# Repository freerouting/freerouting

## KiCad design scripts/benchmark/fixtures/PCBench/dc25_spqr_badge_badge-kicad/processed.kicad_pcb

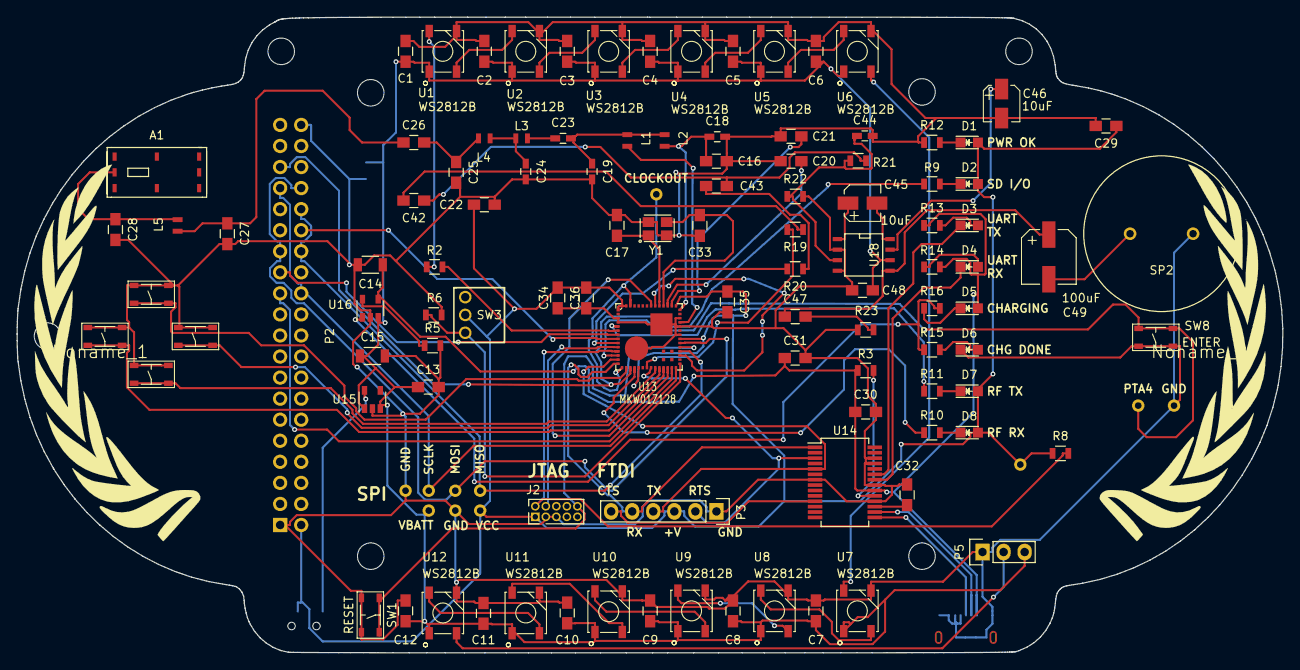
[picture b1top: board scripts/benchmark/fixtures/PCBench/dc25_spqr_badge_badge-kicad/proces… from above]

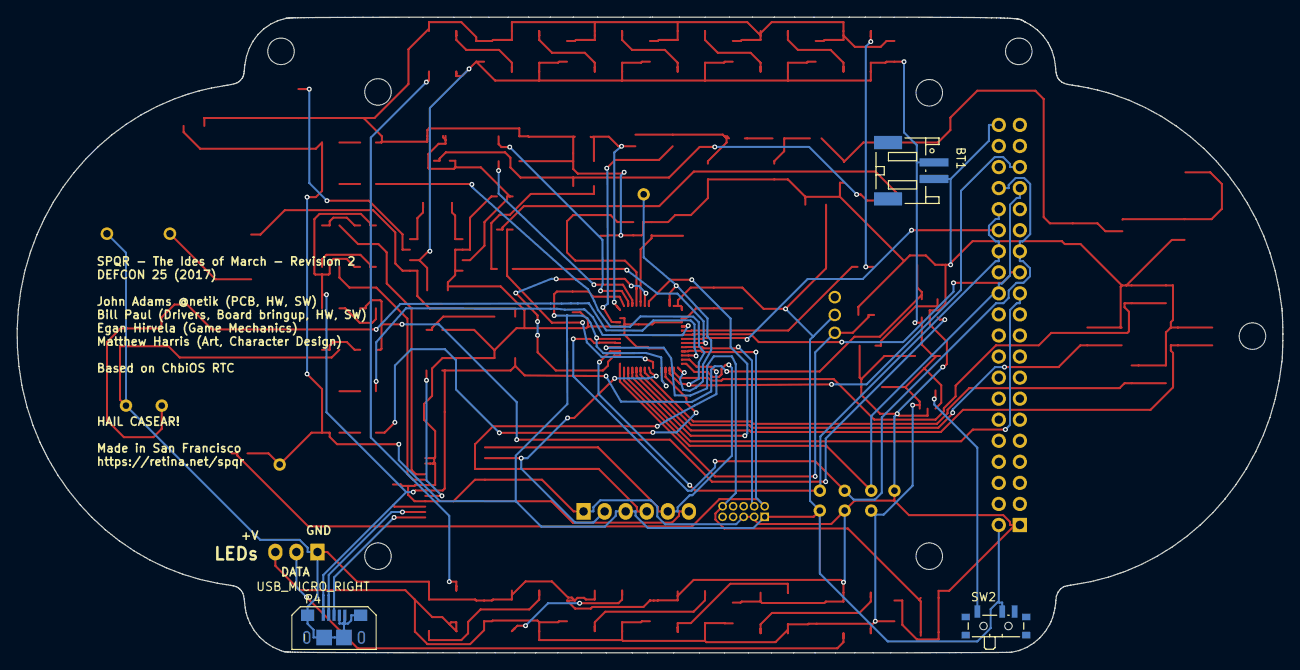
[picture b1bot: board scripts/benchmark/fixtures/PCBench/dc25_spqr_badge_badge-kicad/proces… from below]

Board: 2 copper layers, 152.7 x 76.7 mm, 129 parts (3 on the bottom side), 84 nets.

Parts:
A1: 7488910092_ANTENNA; Antenna_Wurth_7488910092
BT1: Battery 3.7v 1000mAh; JST_PH_S2B-PH-SM4-TB_02x2.00mm_Angled
C1, C2, C3, C4, C5, C6, C7, C8, C9, C10, C11, C12, C20, C21, C22, C30, C32, C34, C35, C36: 0.1uF; C_0805_HandSoldering
C13, C29: 1uF; C_0805_HandSoldering
C14, C15: 10uF; C_1206
C16: 220pF; C_0805_HandSoldering
C17, C33: 11pF; C_0805_HandSoldering
C18, C44: 0.01uF; C_0603_HandSoldering
C19: 2pF; C_0603_HandSoldering
C23: 6.8pF; C_0603_HandSoldering
C24: 7.5pF; C_0603_HandSoldering
C25: 5.6pF; C_0805_HandSoldering
C26: 100pF; C_0805_HandSoldering
C27: 1.2pF; C_0805_HandSoldering
C28: 3.3pF; C_0805_HandSoldering
C31, C42, C43, C48: 10uF; C_0805_HandSoldering
C45, C46: 10uF; MF_Passives-CP4MM
C47: .047uF; C_0805_HandSoldering
C49: 100uF; MF_Passives-CP6.3MM
D1: RED PWROK; LED_0805
D2: GREEN SDIO; LED_0805
D3: RED UTX; LED_0805
D4: GREEN URX; LED_0805
D5: RED (CHARGING); LED_0805
D6: GRN (DONE); LED_0805
D7: RED RFTX; LED_0805
D8: GRN RFRX; LED_0805
H1, H2, H3, H4, H5, H6, H7: CONN_01X01; MountingHole_3.2mm_M3_DIN965
J2: JTAG; Pin_Header_Straight_2x05_Pitch1.27mm
L1: 4.7nH; Neosid_Inductor_SM0603CG
L2: 33nH; Neosid_Inductor_SM0603CG
L3, L4: 0.0068 uH; Neosid_Inductor_SM0603CG
L5: 15nH; Neosid_Inductor_SM0603CG
Noname_1: laurel
Noname_2: laurel_right
P2: CONN_02X20; IDC_HEADER_FEMALE
P3: FTDI BACKUP; Pin_Header_Straight_1x06
P4: USB_MICRO_RIGHT; MF_Connectors-MICROUSB-RIGHT
P5: LED OUT (DNP); Pin_Header_Straight_1x03
R2: 100; R_0805
R3, R6, R23: 10k; R_0805
R5: 2k; R_0805
R8: 10K; R_0805
R9, R10, R11, R12: 220; R_0805
R13, R14, R15, R16, R19, R20, R22: 1k; R_0805
R21: 100k; R_0805
SP2: MODEL TBD; SPEAKER_AST_01708MR_R
SW1: RESET; MF_Switches-TACT4.2MM
SW2: POWERON; SW_SPDT_PCM12
SW3: TM1000
SW4: UP; MF_Switches-TACT4.2MM
SW5: DN; MF_Switches-TACT4.2MM
SW6: LEFT; MF_Switches-TACT4.2MM
SW7: RIGHT; MF_Switches-TACT4.2MM
SW8: ENTER; MF_Switches-TACT4.2MM
TP1: PTA4; Measurement_Point_Round-TH_Small
TP2, TP5, TP10: GND; Measurement_Point_Round-TH_Small
TP3, TP9: VCC; Measurement_Point_Round-TH_Small
TP4: VBAT; Measurement_Point_Round-TH_Small
TP17: SPI_CH1_SCLK; Measurement_Point_Round-TH_Small
TP18: CLOCKOUT; Measurement_Point_Round-TH_Small
TP19: SPI_CH1_MOSI; Measurement_Point_Round-TH_Small
TP20: SPI_CH1_MISO; Measurement_Point_Round-TH_Small
U1, U2, U3, U4, U5, U6, U7, U8, U9, U10, U11, U12: WS2812B; MF_LEDs-WS2812B
U13: MKW01Z128; 98ASA00302D
U14: FT232RL SSOP; SSOP-28_5.3x10.2mm_Pitch0.65mm
U15: MF-REG-SOT235-3.3V-300mA; SOT-23-5
U16: MCP73831T-2ACI/OT; SOT-23-5
U18: LM386; SOIC-8-N
Y1: EXS00A-CS02368; Crystal_EXS00A-CS02368

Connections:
+3V3: C32.1, U14.17
CLOCKOUT: TP18.1, U13.15, U13.54
DACOUT: R20.2, U13.9
DEBUG_SWD_CLK: J2.4, U13.10
DEBUG_SWD_DIO: J2.2, R8.2, U13.11
DIO0: U13.26, U13.49
DISP_CS: P2.23, U13.27
DISP_DC: P2.25, U13.7
DISP_SCK: P2.24, P2.33, TP17.1, U13.28
DISP_SDI(MOSI): P2.27, P2.34, TP19.1, U13.34
DISP_SDO(MISO): P2.28, P2.32, TP20.1, U13.32
GND: BT1.2, C1.2, C2.2, C3.2, C4.2, C5.2, C6.2, C7.2, C8.2, C9.2, C10.2, C11.2, C12.2, C13.2, C14.2, C15.2, C16.2, C17.2, C18.2, C19.2, C20.1, C21.1, C22.2, C24.2, C25.2, C27.2, C28.2, C29.2, C30.2, C31.2, C32.2, C33.2, C34.1, C35.2, C36.2, C44.2, C46.P$2, C48.2, D6.1, J2.3, J2.5, P2.1, P2.40, P3.1, P4.4, P4.5, P4.S3, P4.S4, P4.S5, P4.S6, P5.1, R5.2, R6.2, R12.1, R22.2, R23.2, SP2.2, SW1.P$1, SW1.P$2, SW4.P$1, SW4.P$2, SW5.P$1, SW5.P$2, SW6.P$1, SW6.P$2, SW7.P$1, SW7.P$2, SW8.P$3, SW8.P$4, TP2.1, TP5.1, TP10.1, U1.P$3, U2.P$3, U3.P$3, U4.P$3, U5.P$3, U6.P$3, U7.P$3, U8.P$3, U9.P$3, U10.P$3, U11.P$3, U12.P$3, U13.3, U13.4, U13.36, U13.38, U13.40, U13.61, U13.62, U14.7, U14.18, U14.21, U14.25, U14.26, U15.2, U16.2, U18.2, U18.4, Y1.2, Y1.4
LEDS_IN: R2.1, U13.6
unnamed: A1.2, C28.1, L5.2
unnamed: C17.1, U13.47, Y1.1
unnamed: C19.1, C23.2, L1.2, L2.2
unnamed: C20.2, U13.45
unnamed: C21.2, U13.44
unnamed: C23.1, L3.1
unnamed: C24.1, L3.2, L4.1
unnamed: C25.1, C26.2, L4.2
unnamed: C26.1, C27.1, L5.1
unnamed: C33.1, U13.46, Y1.3
unnamed: C42.1, C43.1, R21.2
unnamed: C42.2, R19.1
unnamed: C43.2, R20.1
unnamed: C44.1, R21.1, R22.1, U18.3
unnamed: C45.P$1, U18.1
unnamed: C45.P$2, U18.8
unnamed: C46.P$1, U18.7
unnamed: C47.1, C49.P$1, U18.5
unnamed: C47.2, R23.1
unnamed: C49.P$2, SP2.1
unnamed: D1.1, R12.2
unnamed: D2.1, R9.2
unnamed: D3.1, U14.23
unnamed: D3.2, R13.2
unnamed: D4.1, U14.22
unnamed: D4.2, R14.2
unnamed: D5.1, R16.1
unnamed: D6.2, R15.2
unnamed: D7.1, R11.2
unnamed: D8.1, R10.2
unnamed: L1.1, U13.39
unnamed: P3.6, U14.11
unnamed: P4.2, U14.16
unnamed: P4.3, U14.15
unnamed: P5.2, U12.P$2
unnamed: R2.2, U1.P$4
unnamed: R3.1, U14.19
unnamed: R5.1, U16.5
unnamed: R15.1, R16.2, U16.1
unnamed: SW2.1, U15.5
unnamed: U1.P$2, U2.P$4
unnamed: U2.P$2, U3.P$4
unnamed: U3.P$2, U4.P$4
unnamed: U4.P$2, U5.P$4
unnamed: U5.P$2, U6.P$4
unnamed: U6.P$2, U7.P$4
unnamed: U7.P$2, U8.P$4
unnamed: U8.P$2, U9.P$4
unnamed: U10.P$2, U11.P$4
unnamed: U9.P$2, U10.P$4
unnamed: U11.P$2, U12.P$4
PTB0: P2.35, R9.1, U13.17
PTB1: R10.1, U13.18
PTE16: R11.1, U13.5
PWM_SOUND: R19.2, U13.21
RESET_TGTMCU: J2.10, SW1.P$3, SW1.P$4, U13.33
RF_RESET: U13.31, U13.48
SWDN: SW5.P$3, SW5.P$4, U13.23
SWENTER: SW8.P$1, SW8.P$2, TP1.1, U13.12
SWL: SW6.P$3, SW6.P$4, U13.25
SWR: SW7.P$3, SW7.P$4, U13.24
SWUP: SW4.P$3, SW4.P$4, U13.16
TILTSENS: R6.1, SW3.1, U13.29
TOUCH_CS: P2.30, U13.8
UART0_CTS: P3.2, U13.22, U14.3
UART_RX: P3.5, U13.14, U14.1
UART_TX: P3.4, U13.13, U14.5
VBAT: BT1.1, C1.1, C2.1, C3.1, C4.1, C5.1, C6.1, C7.1, C8.1, C9.1, C10.1, C11.1, C12.1, C13.1, C15.1, C48.1, P5.3, TP4.1, U1.P$1, U2.P$1, U3.P$1, U4.P$1, U5.P$1, U6.P$1, U7.P$1, U8.P$1, U9.P$1, U10.P$1, U11.P$1, U12.P$1, U15.1, U15.3, U16.3, U18.6
VCC: C22.1, C29.1, C34.2, C35.1, C36.1, D1.2, D2.2, D7.2, D8.2, J2.1, P2.2, P3.3, R8.1, SW2.2, SW3.2, TP3.1, TP9.1, U13.1, U13.19, U13.35, U13.43, U13.55, U13.56
VR_PA: C16.1, C18.1, L2.1, U13.42
VUSB: C14.1, C30.1, C31.1, D5.2, P4.1, R3.2, R13.1, R14.1, U14.20, U16.4

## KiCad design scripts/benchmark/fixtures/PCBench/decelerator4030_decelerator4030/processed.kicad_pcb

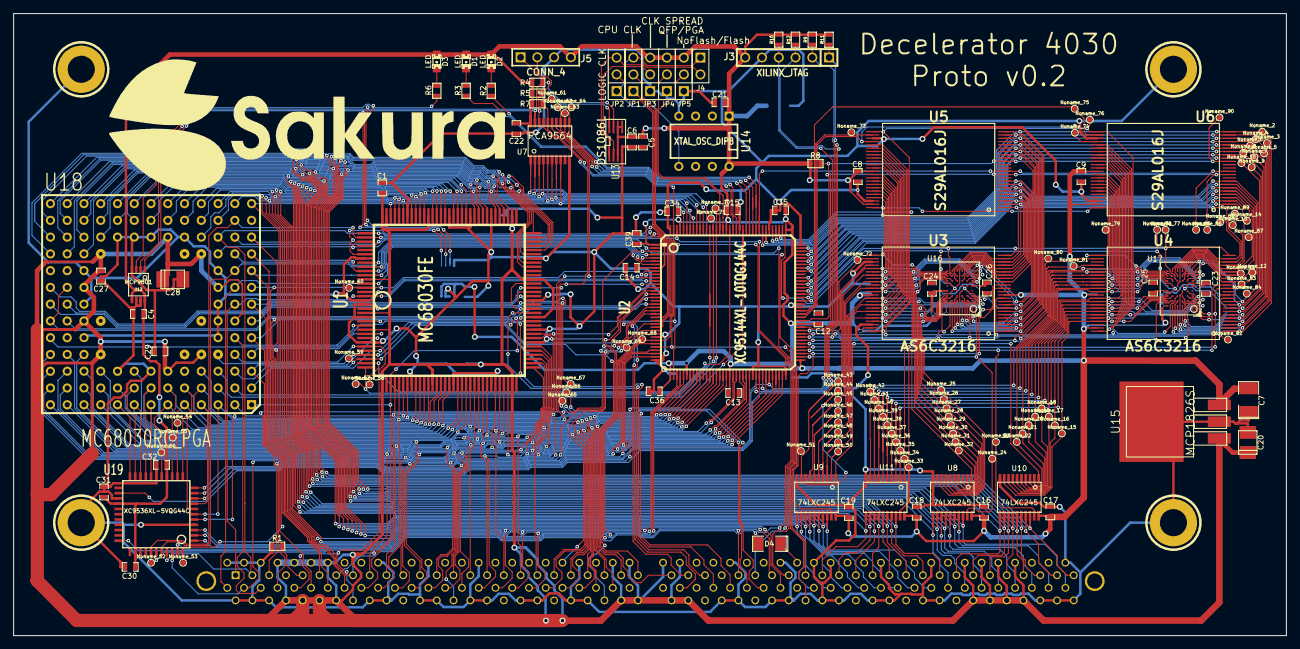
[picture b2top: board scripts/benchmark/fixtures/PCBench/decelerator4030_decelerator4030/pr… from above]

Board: 2 copper layers, 192.9 x 94.3 mm, 180 parts (0 on the bottom side), 206 nets.

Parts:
C1, C27: 0.22uF; SM0603_Capa
C2, C28: 22uF; c_tant_B
C3, C29: 220pF; SM0603_Capa
C4, C8, C9, C10, C11, C12, C13, C14, C15, C16, C17, C18, C19, C22, C23, C24, C25, C26, C30, C31, C32, C33, C34, C35, C36, C37, C38, C39: 100nF; SM0603_Capa
C5: 0.1uF; SM0603_Capa
C6, C21: 0.01uF; SM0603_Capa
C7, C40, C41: 1uF; SM1210L
C20: 4,7uF; c_tant_B
CON1: A3000/A4000_LOCAL_BUS_SLOT; 8817-200-170S-F
D1, D2, D3: LED; LED-0805
D4: 1N4148; SM1206POL
Hole_4mm, Hole_4mm_2, Hole_4mm_3, Hole_4mm_4: P***; hole_4mm
J3: XILINX_JTAG; PIN_ARRAY-6X1
J4: CONN_2; PIN_ARRAY_2X1
J5: CONN_4; PIN_ARRAY_4x1
JP1: CPU CLK; PIN_ARRAY_3X1
JP2: LOGIC CLK; PIN_ARRAY_3X1
JP3: CLK SPREAD; PIN_ARRAY_3X1
JP4: QFP/PGA; PIN_ARRAY_3X1
JP5: NoFlash/Flash; PIN_ARRAY_3X1
Noname_1: LOGO
Noname_2, Noname_3, Noname_4, Noname_5, Noname_6, Noname_7, Noname_8, Noname_9, Noname_10, Noname_11, Noname_12, Noname_13, Noname_14, Noname_15, Noname_16, Noname_17, Noname_18, Noname_19, Noname_20, Noname_21, Noname_22, Noname_23, Noname_24, Noname_25, Noname_26, Noname_27, Noname_28, Noname_29, Noname_30, Noname_31, Noname_32, Noname_33, Noname_34, Noname_35, Noname_36, Noname_37, Noname_38, Noname_39, Noname_40, Noname_41, Noname_42, Noname_43, Noname_44, Noname_45, Noname_46, Noname_47, Noname_48, Noname_49, Noname_50, Noname_51, Noname_52, Noname_53, Noname_54, Noname_55, Noname_56, Noname_57, Noname_58, Noname_59, Noname_60, Noname_61, Noname_62, Noname_63, Noname_64, Noname_65, Noname_66, Noname_67, Noname_68, Noname_69, Noname_70, Noname_71, Noname_72, Noname_73, Noname_74, Noname_75, Noname_76, Noname_77, Noname_78, Noname_79, Noname_80, Noname_81, Noname_82, Noname_83, Noname_84, Noname_85, Noname_86, Noname_87, Noname_88, Noname_89, Noname_90: PINTST_0.8
R1: 100; SM0603
R2, R3, R6: k22; SM0603
R4, R5, R7, R8, R9, R10, R11, R12: 4k7; SM0603
U1: MC68030FE; PQFP132M
U2: XC95144XL-10TQG144C; TQFP144
U3, U4: AS6C3216; TSOP48
U5, U6: S29AL016J; TSOP48
U7: PCA9564; tssop-20
U8, U9, U10, U11: 74LXC245; tssop-20
U12, U20: MCP9801; MSOP-8
U13: DS1086L; uMAX-uSOP_8
U14: XTAL_OSC_DIP8; DIP-8__300
U15: MCP1826S; D2PAK3
U16, U17: IS66WVE4M16; tfbga48
U18: MC68030RC_PGA; MC68030
U19: XC9536XL-5VQG44C; VQFP44

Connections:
68030CLK: JP1.2, Noname_53.1, U1.6, U2.38, U18.E1, U19.44
+3.3V: C4.2, C5.1, C6.1, C7.2, C8.1, C9.1, C10.1, C11.1, C12.1, C13.1, C14.1, C15.1, C16.1, C17.1, C18.1, C19.1, C21.1, C22.2, C23.1, C24.1, C25.1, C26.1, C30.1, C31.1, C32.1, C33.2, C34.1, C35.1, C36.1, C37.1, C38.1, C39.1, C40.2, C41.2, D1.1, D2.1, D3.1, J3.6, J5.4, JP3.3, JP4.3, JP5.3, R4.1, R5.1, R7.2, R8.1, R9.1, R10.1, R11.1, R12.1, U2.1, U2.8, U2.37, U2.42, U2.55, U2.73, U2.84, U2.109, U2.127, U2.141, U3.12, U3.37, U3.47, U4.12, U4.37, U4.47, U5.37, U5.47, U6.37, U6.47, U7.20, U8.20, U9.20, U10.20, U11.20, U12.5, U12.8, U13.3, U13.5, U13.6, U14.1, U14.8, U15.3, U16.A6, U16.D6, U16.E1, U17.A6, U17.D6, U17.E1, U19.15, U19.26, U19.35, U20.5, U20.8
+5V: C1.1, C2.1, C3.1, C20.1, C27.1, C28.1, C29.1, CON1.14, CON1.15, CON1.18, CON1.19, CON1.22, CON1.23, CON1.26, CON1.27, CON1.94, CON1.95, CON1.98, CON1.99, CON1.102, CON1.103, CON1.106, CON1.107, CON1.174, CON1.175, CON1.178, CON1.179, CON1.182, CON1.183, CON1.186, CON1.187, U1.4, U1.8, U1.18, U1.30, U1.49, U1.63, U1.72, U1.85, U1.105, U1.115, U1.116, U1.128, U15.1, U18.C6, U18.D4, U18.D10, U18.F2, U18.F11, U18.H3, U18.H11, U18.K4, U18.K10, U18.L6
/A0: CON1.36, U1.21, U2.11, U7.14, U18.A2
/A1: CON1.40, U1.22, U2.13, U7.15, U18.C4
/A2: CON1.44, U1.59, U2.14, U18.D13
/A3: CON1.48, U1.58, U2.15, U18.D12
/A4: CON1.52, U1.56, U2.71, U18.C13
/A5: CON1.56, U1.55, U2.69, U18.C12
/A6: CON1.60, U1.54, U2.66, U18.D11
/A7: CON1.64, U1.53, U2.33, U18.B13
/A8: CON1.33, U1.52, U2.34, U18.B12
/A9: CON1.37, U1.51, U2.60, U18.C11
/A10: CON1.41, U1.48, U2.70, U18.A13
/A11: CON1.45, U1.47, U2.57, U18.C10
/A12: CON1.49, U1.46, U2.61, U18.B11
/A13: CON1.53, U1.45, U2.68, U18.A12
/A14: CON1.57, U1.43, U2.58, U18.B10
/A15: CON1.61, U1.42, U2.64, U18.A11
/A16: CON1.65, U1.41, U2.54, U18.B9
/A17: CON1.69, U1.40, U2.59, U18.A10
/A18: CON1.73, U1.39, U2.51, U18.C8
/A19: CON1.77, U1.38, U2.56, U18.A9, U19.22
/A20: CON1.81, U1.37, U2.53, U18.B8, U19.21
/A21: CON1.85, U1.36, U2.52, U18.A8, U19.20
/A22: CON1.89, U1.34, U2.50, U18.B7, U19.19
/A23: CON1.93, U1.33, U2.49, U18.A7, U19.18
/A24: Noname_56.1, U1.32, U18.A6, U19.16
/A25: Noname_55.1, U1.31, U18.B6, U19.14
/A26: Noname_54.1, U1.29, U18.A5, U19.13
/A27: CON1.80, U1.28, U2.48, U18.B5, U19.12
/A28: CON1.84, U1.27, U2.46, U18.A4, U19.8
/A29: CON1.88, U1.26, U2.45, U18.B4, U19.7
/A30: CON1.92, U1.24, U2.44, U18.A3, U19.6
/A31: CON1.96, U1.23, U2.43, U18.B3, U19.5
/ARM0: Noname_76.1, U2.111, U3.48, U4.48, U5.25, U6.25, U16.C4, U17.C4
/ARM1: Noname_2.1, U2.113, U3.1, U4.1, U5.24, U6.24, U16.A5, U17.A5
/ARM2: Noname_3.1, U2.115, U3.2, U4.2, U5.23, U6.23, U16.B4, U17.B4
/ARM3: Noname_4.1, U2.116, U3.3, U4.3, U5.22, U6.22, U16.A4, U17.A4
/ARM4: Noname_5.1, U2.107, U3.4, U4.4, U5.21, U6.21, U16.D3, U17.D3
/ARM5: Noname_6.1, U2.106, U3.5, U4.5, U5.20, U6.20, U16.A3, U17.A3
/ARM6: Noname_7.1, U2.105, U3.6, U4.6, U5.19, U6.19, U16.B3, U17.B3
/ARM7: Noname_8.1, U2.104, U3.7, U4.7, U5.18, U6.18, U16.C3, U17.C3
/ARM8: Noname_83.1, U2.100, U3.16, U4.16, U5.8, U6.8, U16.F3, U17.F3
/ARM9: Noname_12.1, U2.98, U3.17, U4.17, U5.7, U6.7, U16.H2, U17.H2
/ARM10: Noname_11.1, U2.97, U3.18, U4.18, U5.6, U6.6, U16.G3, U17.G3
/ARM11: Noname_87.1, U2.96, U3.19, U4.19, U5.5, U6.5, U16.H3, U17.H3
/ARM12: Noname_14.1, U2.95, U3.20, U4.20, U5.4, U6.4, U16.E4, U17.E4
/ARM13: Noname_13.1, U2.94, U3.21, U4.21, U5.3, U6.3, U16.H4, U17.H4
/ARM14: Noname_89.1, U2.93, U3.22, U4.22, U5.2, U6.2, U16.G4, U17.G4
/ARM15: Noname_88.1, U2.92, U3.23, U4.23, U5.1, U6.1, U16.H5, U17.H5
/ARM16: Noname_79.1, U2.112, U3.25, U4.25, U5.48, U6.48, U16.H6, U17.H6
/ARM17: Noname_9.1, U2.103, U3.8, U4.8, U5.17, U6.17, U16.E3, U17.E3
/ARM18: Noname_10.1, U2.102, U3.9, U4.9, U5.16, U6.16, U16.G2, U17.G2
/ARM19: Noname_84.1, U2.101, U3.10, U4.10, U5.9, U6.9, U16.H1, U17.H1
/ARM20: Noname_77.1, U2.91, U3.24, U4.24, U16.F4, U17.F4
/ARM21: Noname_78.1, U2.110, U16.D4, U17.D4
/D0: CON1.172, U1.75, U8.11, U18.K13
/D1: CON1.176, U1.76, U8.12, U18.K12
/D2: CON1.180, U1.78, U8.13, U18.L13
/D3: CON1.184, U1.79, U8.14, U18.M13
/D4: CON1.188, U1.80, U8.15, U18.L12
/D5: CON1.192, U1.81, U8.16, U18.K11
/D6: CON1.196, U1.82, U8.17, U18.M12
/D7: CON1.200, U1.83, U8.18, U18.L11
/D8: CON1.168, U1.86, U9.18, U18.N13
/D9: CON1.164, U1.87, U9.17, U18.M11
/D10: CON1.160, U1.88, U9.16, U18.L10
/D11: CON1.156, U1.89, U9.15, U18.N12
/D12: CON1.152, U1.91, U9.14, U18.M10
/D13: CON1.148, U1.92, U9.13, U18.N11
/D14: CON1.144, U1.93, U9.12, U18.M9
/D15: CON1.140, U1.94, U9.11, U18.N10
/D16: CON1.169, U1.96, U10.11, U18.N9
/D17: CON1.173, U1.97, U10.12, U18.M8
/D18: CON1.177, U1.98, U10.13, U18.N8
/D19: CON1.181, U1.99, U10.14, U18.N7
/D20: CON1.185, U1.101, U10.15, U18.M7
/D21: CON1.189, U1.102, U10.16, U18.N6
/D22: CON1.193, U1.103, U10.17, U18.M6
/D23: CON1.197, U1.104, U10.18, U18.N5
/D24: CON1.165, U1.106, U2.133, U7.1, U11.18, U18.M5
/D25: CON1.161, U1.107, U2.134, U7.2, U11.17, U18.N4
/D26: CON1.157, U1.108, U2.135, U7.3, U11.16, U18.N3
/D27: CON1.153, U1.109, U2.136, U7.4, U11.15, U18.M4
/D28: CON1.149, U1.111, U2.137, U7.5, U11.14, U18.N2
/D29: CON1.145, U1.112, U2.138, U7.6, U11.13, U18.M3
/D30: CON1.141, U1.113, U2.139, U7.7, U11.12, U18.L4
/D31: CON1.137, U1.114, U2.140, U7.8, U11.11, U18.N1
/DRM0: Noname_25.1, U3.45, U5.29, U8.9, U16.B6
/DRM1: Noname_26.1, U3.43, U5.31, U8.8, U16.C5
/DRM2: Noname_27.1, U3.41, U5.33, U8.7, U16.C6
/DRM3: Noname_28.1, U3.39, U5.35, U8.6, U16.D5
/DRM4: Noname_29.1, U3.36, U5.38, U8.5, U16.E5
/DRM5: Noname_30.1, U3.34, U5.40, U8.4, U16.F6
/DRM6: Noname_31.1, U3.32, U5.42, U8.3, U16.F5
/DRM7: Noname_32.1, U3.30, U5.44, U8.2, U16.G6
/DRM8: Noname_50.1, U3.44, U5.30, U9.2, U16.B1
/DRM9: Noname_49.1, U3.42, U5.32, U9.3, U16.C2
/DRM10: Noname_48.1, U3.40, U5.34, U9.4, U16.C1
/DRM11: Noname_47.1, U3.38, U5.36, U9.5, U16.D2
/DRM12: Noname_46.1, U3.35, U5.39, U9.6, U16.E2
/DRM13: Noname_45.1, U3.33, U5.41, U9.7, U16.F1
/DRM14: Noname_44.1, U3.31, U5.43, U9.8, U16.F2
/DRM15: Noname_43.1, U3.29, U5.45, U9.9, U16.G1
/DRM16: Noname_15.1, U4.45, U6.29, U10.9, U17.B6
/DRM17: Noname_16.1, U4.43, U6.31, U10.8, U17.C5
/DRM18: Noname_17.1, U4.41, U6.33, U10.7, U17.C6
/DRM19: Noname_18.1, U4.39, U6.35, U10.6, U17.D5
/DRM20: Noname_19.1, U4.36, U6.38, U10.5, U17.E5
/DRM21: Noname_20.1, U4.34, U6.40, U10.4, U17.F6
/DRM22: Noname_21.1, U4.32, U6.42, U10.3, U17.F5
/DRM23: Noname_22.1, U4.30, U6.44, U10.2, U17.G6
/DRM24: Noname_35.1, U4.44, U6.30, U11.2, U17.B1
/DRM25: Noname_36.1, U4.42, U6.32, U11.3, U17.C2
/DRM26: Noname_37.1, U4.40, U6.34, U11.4, U17.C1
/DRM27: Noname_38.1, U4.38, U6.36, U11.5, U17.D2
/DRM28: Noname_39.1, U4.35, U6.39, U11.6, U17.E2
/DRM29: Noname_40.1, U4.33, U6.41, U11.7, U17.F1
/DRM30: Noname_41.1, U4.31, U6.43, U11.8, U17.F2
/DRM31: Noname_42.1, U4.29, U6.45, U11.9, U17.G1
/IPL0: CON1.120, Noname_65.1, U1.70, U18.H13
/IPL1: CON1.124, Noname_66.1, U1.69, U18.G13
/IPL2: CON1.128, Noname_67.1, U1.68, U18.G12
CPUCLK_EXP: CON1.135, JP1.1, U2.32
FC0: CON1.20, U1.12, U18.D2
FC1: CON1.24, U1.10, U18.C1
FC2: CON1.125, U1.9, U18.D1
GND: C1.2, C2.2, C3.2, C4.1, C5.2, C6.2, C7.1, C8.2, C9.2, C10.2, C14.2, C15.2, C16.2, C17.2, C18.2, C19.2, C20.2, C21.2, C22.1, C27.2, C28.2, C29.2, C30.2, C31.2, C32.2, C33.1, C34.2, C35.2, C36.2, C37.2, C38.2, C39.2, C40.1, C41.1, CON1.2, CON1.3, CON1.6, CON1.7, CON1.10, CON1.11, CON1.35, CON1.38, CON1.39, CON1.47, CON1.50, CON1.51, CON1.59, CON1.62, CON1.63, CON1.71, CON1.75, CON1.83, CON1.86, CON1.87, CON1.115, CON1.118, CON1.119, CON1.127, CON1.130, CON1.131, CON1.138, CON1.139, CON1.142, CON1.143, CON1.151, CON1.154, CON1.155, CON1.163, CON1.166, CON1.167, CON1.191, CON1.195, CON1.198, CON1.199, Hole_4mm.1, Hole_4mm_2.1, Hole_4mm_3.1, Hole_4mm_4.1, J3.5, J5.3, JP3.1, JP4.1, JP5.1, R1.1, U1.1, U1.2, U1.5, U1.11, U1.25, U1.35, U1.44, U1.57, U1.60, U1.66, U1.67, U1.77, U1.90, U1.95, U1.100, U1.110, U1.123, U2.29, U2.36, U2.62, U2.72, U2.89, U2.90, U2.108, U2.114, U2.123, U2.144, U3.27, U3.46, U5.27, U5.46, U6.27, U6.46, U7.10, U8.10, U9.10, U10.10, U11.10, U12.4, U12.6, U12.7, U13.4, U14.4, U15.2, U18.C7, U18.C9, U18.E3, U18.E11, U18.F3, U18.G3, U18.G11, U18.J3, U18.J11, U18.L5, U18.L7, U18.L8, U18.L9, U19.4, U19.17, U19.25, U20.4, U20.6, U20.7
IDBUS_DIR: Noname_34.1, U2.78, U8.1, U9.1, U10.1, U11.1
IPEND: CON1.116, U1.62, U18.E13
LOGIC_CLK: JP2.2, Noname_68.1, U2.30, U19.43
MA24: CON1.68, U2.39, U19.3
MA25: CON1.72, U2.40, U19.2
MA26: CON1.76, U2.41, U19.1
unnamed: CON1.17, R1.2
unnamed: CON1.101, U1.15, U18.C2
unnamed: R2.1, U2.118
unnamed: D2.2, R2.2
unnamed: R3.1, U2.119
unnamed: D1.2, R3.2
unnamed: R6.1, U12.3, U20.3
unnamed: J4.1, JP1.3, JP2.1, U14.5
unnamed: J4.2, JP2.3, U13.1
unnamed: JP3.2, U13.2
unnamed: D3.2, R6.2
NO_FLASH: JP5.2, U2.128
R_W: CON1.5, U1.117, U2.23, U18.L3, U19.41
SCL: J5.2, R5.2, U7.18, U12.2, U13.8, U20.2
SDA: J5.1, R4.2, U7.19, U12.1, U13.7, U20.1
SIZ0: CON1.121, U1.120, U2.142, U18.L2
SIZ1: CON1.129, U1.119, U2.2, U18.K3
TCK: J3.4, R10.2, U2.67, U19.11
TDI: J3.2, R9.2, U2.63
TDO1: U2.122, U19.9
TDO2: J3.3, R12.2, U19.24
TMS: J3.1, R11.2, U2.65, U19.10
_AS: CON1.133, U1.125, U2.4, U18.J2, U19.40
_AVEC: CON1.12, U1.7, U18.E2
_BERR: CON1.29, D4.2, Noname_60.1, U1.130, U2.9, U18.H1
_BG: CON1.105, U2.22
_BGACK: CON1.8, U2.25, U19.42
_BGACK_PGA: Noname_70.1, U2.130, U18.C3
_BGACK_QFP: Noname_57.1, U1.17, U2.132
_BG_PGA: Noname_71.1, U2.131, U18.B2
_BG_QFP: Noname_58.1, U1.16, U2.126
_BR: CON1.25, U1.20, U2.19, U18.A1
_CBACK: CON1.28, U1.127, U2.6, U18.J1
_CBREQ: CON1.32, U1.126, U2.5, U18.K1
_CIIN: CON1.132, U1.122, U2.26, U18.L1
_CPURST: CON1.109, U1.64, U18.F12
_DS: CON1.97, U1.124, U2.3, U18.K2
_DSACK0: CON1.91, U1.3, U2.16, U18.F1
_DSACK1: CON1.1, U1.132, U2.12, U18.G2
_ECS: Noname_52.1, U1.118, U2.24, U18.M2, U19.38
_EMUL: CON1.31, U1.65, U1.71, U18.F13, U18.H12
_FLASH_BUSY: Noname_90.1, R8.2, U2.83, U5.15, U6.15
_FLASH_HI_CE: Noname_75.1, U2.88, U6.26
_FLASH_LO_CE: Noname_73.1, U2.87, U5.26
_FLASH_OE: Noname_74.1, U2.86, U5.28, U6.28
_FLASH_WE: Noname_86.1, U2.85, U5.11, U6.11
_FPUCS: CON1.134, D4.1
_HLT: CON1.4, U1.129, U2.7, U18.H2
_I2CCE: Noname_62.1, U2.124, U7.13
_I2CINT: Noname_61.1, R7.1, U2.125, U7.16
_I2CRD: Noname_63.1, U2.121, U7.12
_I2CWR: Noname_64.1, U2.120, U7.11
_IDBUS_LLB: Noname_24.1, U2.74, U3.15, U8.19, U16.A1
_IDBUS_LUB: Noname_51.1, U2.75, U3.14, U9.19, U16.B2
_IDBUS_ULB: Noname_23.1, U2.76, U4.15, U10.19, U17.A1
_IDBUS_UUB: Noname_33.1, U2.77, U4.14, U11.19, U17.B2
_INT2: CON1.82, U2.20
_MAPEN: Noname_69.1, U2.28, U19.39
_OCS: Noname_59.1, U1.14, U2.27, U18.D3
_PGA/QFP: JP4.2, U2.129
_RAMSLOT: CON1.16, U2.35
_RESET: CON1.117, U2.143, U7.17, U19.33
_RESET_CPLD: Noname_85.1, U2.117, U5.12, U6.12
_RMC: CON1.108, U1.13, U2.17, U18.B1
_SBR: CON1.9, U2.21
_SRAM_HI_CE: Noname_80.1, U2.79, U4.26, U17.B5
_SRAM_LO_CE: Noname_72.1, U2.80, U3.26, U16.B5
_SRAM_OE: Noname_81.1, U2.81, U3.28, U4.28, U16.A2, U17.A2
_SRAM_WE: Noname_82.1, U2.82, U3.11, U4.11, U16.G5, U17.G5
_STERM: CON1.21, U1.131, U2.10, U18.G1
_WAIT: CON1.55, U2.31

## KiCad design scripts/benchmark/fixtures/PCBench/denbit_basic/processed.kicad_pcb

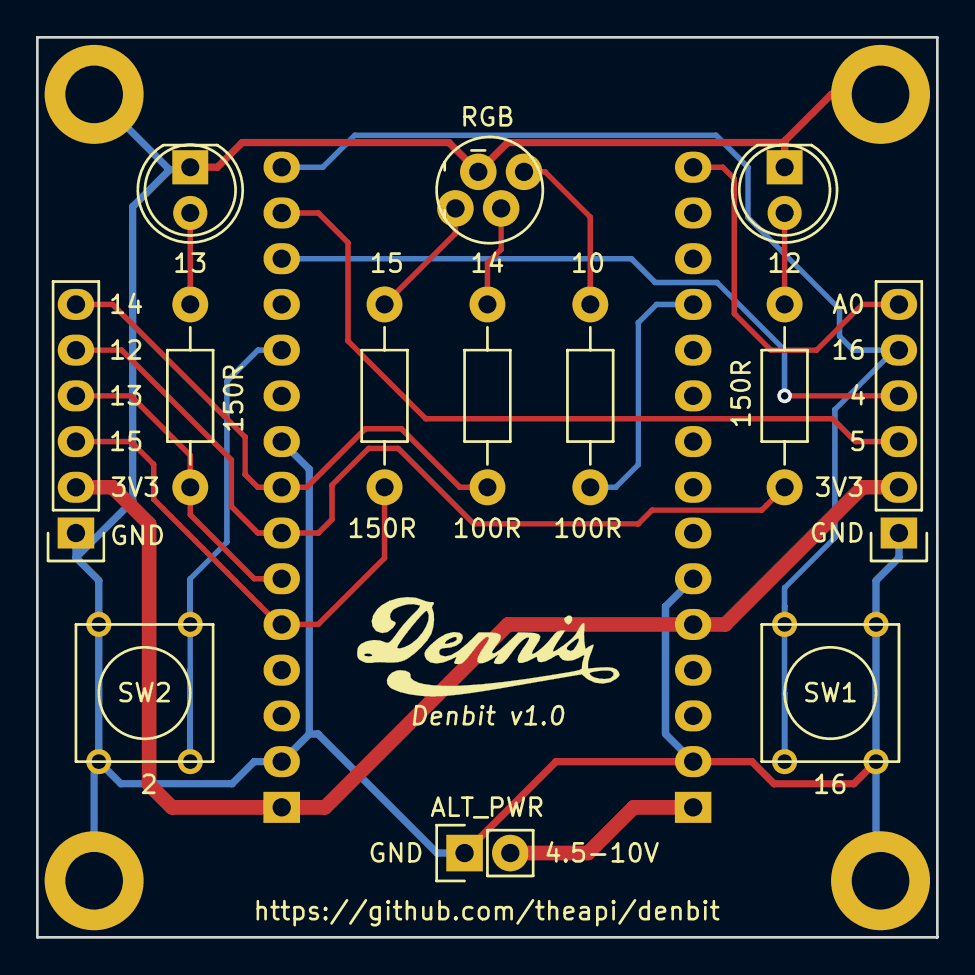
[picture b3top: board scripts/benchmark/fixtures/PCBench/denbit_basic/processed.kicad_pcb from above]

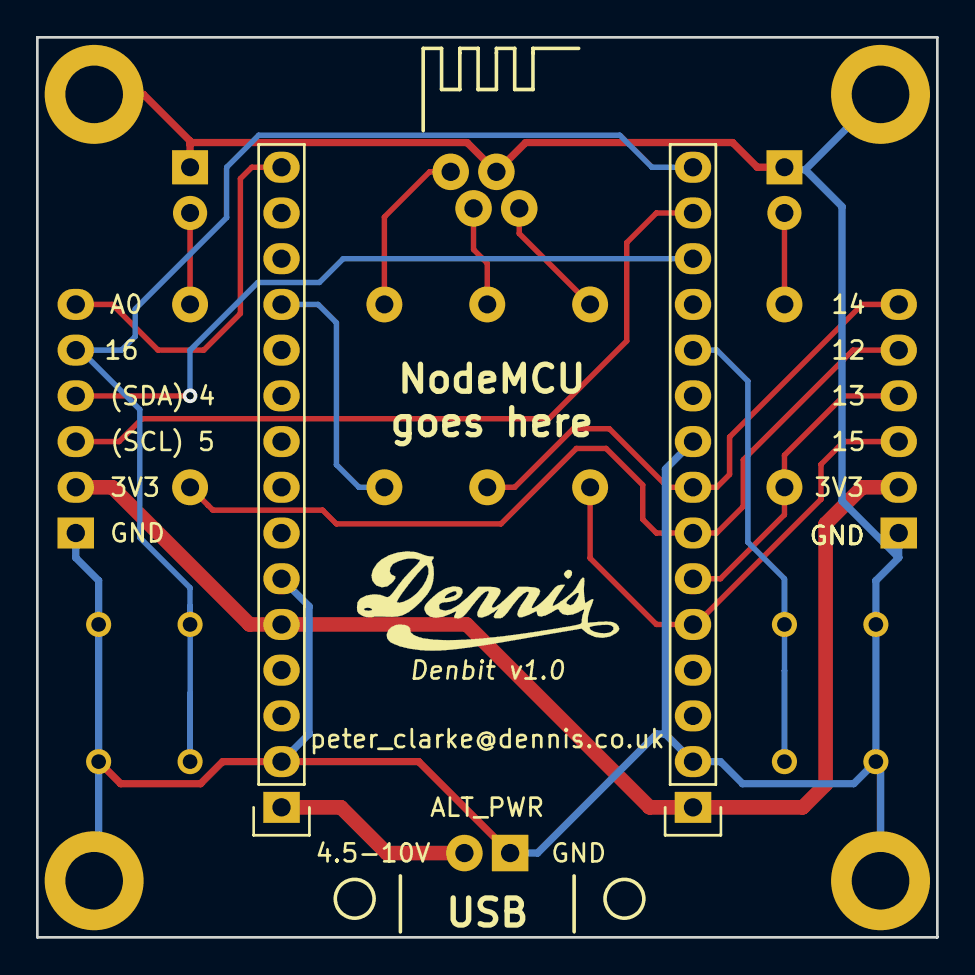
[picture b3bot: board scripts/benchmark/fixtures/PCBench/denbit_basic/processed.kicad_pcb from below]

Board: 2 copper layers, 50.0 x 50.0 mm, 19 parts (2 on the bottom side), 18 nets.

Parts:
D1, D4: LED; LED-5MM
D2: LED_RCBG; LED-RGB-5MM_Common_Cathode_zig_zag
P1: EXT_PWR; Pin_Header_Straight_1x02
P2, P3: CONN_01X15; Socket_Strip_Straight_1x15
P4, P9: CONN_01X06; Socket_Strip_Straight_1x06
P5, P6, P7, P8: CONN_01X01; MountingHole_3.2mm_M3_ISO14580_Pad
R3, R4, R6: 150R; Resistor_Horizontal_RM10mm
R5, R7: 100R; Resistor_Horizontal_RM10mm
SW1, SW2: SW_PUSH; SW_PUSH_SMALL

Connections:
3V3: P2.5, P3.1, P4.2, P9.2
/RGB_BLUE: D2.4, R7.1
/RGB_GREEN: D2.3, R5.1
/RGB_RED: D2.1, R6.1
/S_GREEN: D1.2, R3.1
/S_RED: D4.2, R4.1
ADC0: P2.15, P4.6
GND: D1.1, D2.2, D4.1, P1.1, P2.2, P2.6, P3.2, P3.9, P4.1, P5.1, P6.1, P7.1, P8.1, P9.1, SW1.1, SW2.1
GPIO2: P3.11, SW2.2
GPIO4: P3.13, P4.4
GPIO5: P3.14, P4.3
GPIO10: P2.12, R7.2
GPIO12: P3.7, P9.5, R4.2
GPIO13: P3.6, P9.4, R3.2
GPIO14: P3.8, P9.6, R5.2
GPIO15: P3.5, P9.3, R6.2
GPIO16: P3.15, P4.5, SW1.2
VIN: P1.2, P2.1
